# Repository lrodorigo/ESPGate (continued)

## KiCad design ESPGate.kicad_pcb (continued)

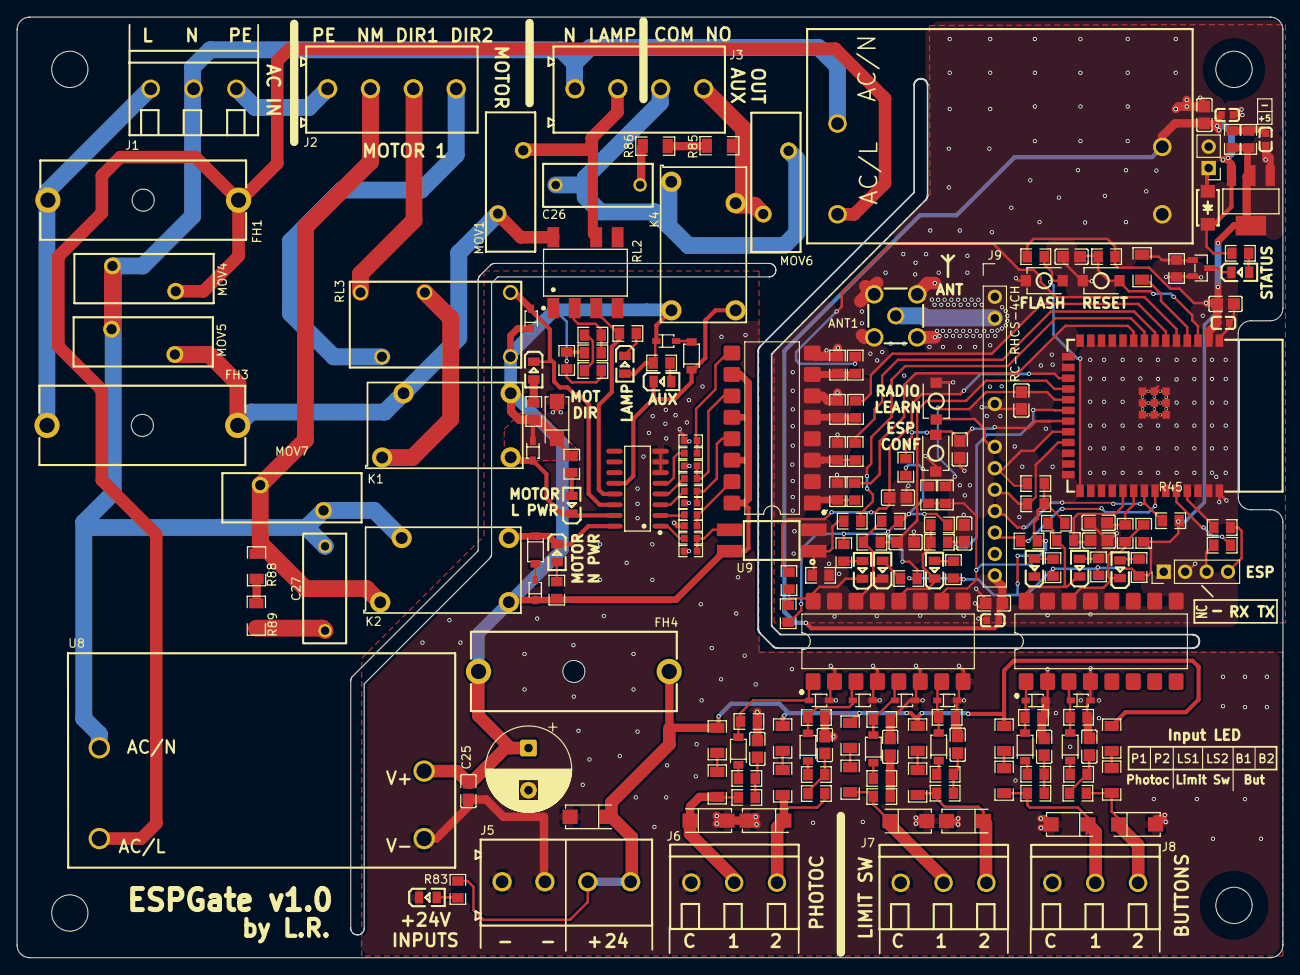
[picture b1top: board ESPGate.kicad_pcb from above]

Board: 2 copper layers, 150.1 x 111.5 mm, 203 parts (0 on the bottom side), 125 nets.

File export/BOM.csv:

"Reference","Qty","Value","LCSC Part","DNP","Exclude from Simulation","Exclude from Position Files","Description"
"C5,C18","2","470uF","","DNP","","${EXCLUDE_FROM_POS_FILES}","Polarized capacitor"
"J4","1","Conn_01x04_Pin","","","","${EXCLUDE_FROM_POS_FILES}","Generic connector, single row, 01x04, script generated"
"R1","1","1","C25271","","","${EXCLUDE_FROM_POS_FILES}","Resistor"
"R2,R16,R22,R25,R29,R35,R44","7","330","C17630","","","${EXCLUDE_FROM_POS_FILES}","Resistor"
"R3,R4,R6,R9,R11,R14,R18,R20,R21,R23,R24,R26,R27,R53,R54,R55,R56,R57,R58,R83","20","10k","C17414","","","${EXCLUDE_FROM_POS_FILES}","Resistor"
"R7,R8,R10,R12,R13,R15,R17,R19","8","1.2k","C17379","","","${EXCLUDE_FROM_POS_FILES}","Resistor"
"R30,R31,R32,R33,R34,R37","6","6.8k","C17772","","","${EXCLUDE_FROM_POS_FILES}","Resistor"
"R36,R39,R40,R41,R42,R43,R46,R47,R48,R49,R50,R51,R77,R78,R79,R80,R81,R82","18","1k","C17513","","","${EXCLUDE_FROM_POS_FILES}","Resistor"
"R65,R66,R67,R68,R69,R70","6","100","C17408","","","${EXCLUDE_FROM_POS_FILES}","Resistor"
"R5,R28,R38,R45,R52","5","100","C17901","","","${EXCLUDE_FROM_POS_FILES}","Resistor"
"R59,R60,R61,R62,R63,R64","6","1k","C4410","","","${EXCLUDE_FROM_POS_FILES}","Resistor"
"R71,R72,R73,R74,R75,R76","6","2k","C17944","","","${EXCLUDE_FROM_POS_FILES}","Resistor"
"C1,C2,C7","3","10uF","C19702","","","${EXCLUDE_FROM_POS_FILES}","Unpolarized capacitor"
"C3,C6,C8,C9,C10,C12,C13,C14,C15,C16,C25","11","100nF","C28233","","","${EXCLUDE_FROM_POS_FILES}","Unpolarized capacitor"
"C4","1","1uF","C28323","","","${EXCLUDE_FROM_POS_FILES}","Unpolarized capacitor"
"C19,C20,C21,C22,C23,C24","6","4.7uF","C1779","","","${EXCLUDE_FROM_POS_FILES}","Unpolarized capacitor"
"C11,C17","2","22nF","C390050","","","${EXCLUDE_FROM_POS_FILES}",""
"J1,J6,J7,J8","4","Screw_Terminal_01x03","","","","${EXCLUDE_FROM_POS_FILES}","Generic screw terminal, single row, 01x03, script generated (kicad-library-utils/schlib/autogen/connector/)"
"J2,J3,J5","3","Screw_Terminal_01x04","","","","${EXCLUDE_FROM_POS_FILES}","Generic screw terminal, single row, 01x04, script generated (kicad-library-utils/schlib/autogen/connector/)"
"FH1,FH2,FH3,FH4","4","PTF-77","C717030","","","${EXCLUDE_FROM_POS_FILES}",""
"NTC1","1","KH-2.54PH180-1X3P-L11.5","C2932698","DNP","","${EXCLUDE_FROM_POS_FILES}",""
"LED1,LED12","2","17-21SUYC/TR8","C2297","","","${EXCLUDE_FROM_POS_FILES}",""
"LED2,LED3,LED4,LED6,LED7,LED8,LED9,LED10,LED11","9","NCD0805R1","C84256","","","${EXCLUDE_FROM_POS_FILES}",""
"LED5","1","0805G (Green)","C2297","","","${EXCLUDE_FROM_POS_FILES}",""
"U8","1","IRM-10-24_C5127809","C5127809","","","${EXCLUDE_FROM_POS_FILES}",""
"U1","1","IRM-05-5","C48603696","","","${EXCLUDE_FROM_POS_FILES}",""
"RL3","1","G5Q-14-DC24","C397242","","","${EXCLUDE_FROM_POS_FILES}",""
"RL4","1","HF140FF/024-2ZSTF","C5322992","","","${EXCLUDE_FROM_POS_FILES}",""
"RN1","1","4x 10k","C29718","","","${EXCLUDE_FROM_POS_FILES}",""
"MOV1,MOV2,MOV3,MOV4,MOV5","5","14D471K_C8852","C8852","","","${EXCLUDE_FROM_POS_FILES}","Voltage dependent resistor"
"D5","1","SS14","C2480","","","${EXCLUDE_FROM_POS_FILES}",""
"D2,D18,D19,D20,D21,D22,D23,D24","8","SMAJ26A-C148225","C148225","","","${EXCLUDE_FROM_POS_FILES}",""
"RL1,RL2","2","BC2223A","C596513","","","${EXCLUDE_FROM_POS_FILES}",""
"D4,D12,D13,D14,D15,D16,D17","7","BZT52C10_C19077408","C19077408","","","${EXCLUDE_FROM_POS_FILES}",""
"D1,D3","2","1N4148WS T4","C2128","","","${EXCLUDE_FROM_POS_FILES}",""
"D6,D7,D8,D9,D10,D11","6","1N4148","C2128","","","${EXCLUDE_FROM_POS_FILES}",""
"U5","1","ULN2003ADR","C7512","","","${EXCLUDE_FROM_POS_FILES}","High Voltage, High Current Darlington Transistor Arrays, SOIC16/SOIC16W/DIP16/TSSOP16"
"U2","1","AMS1117-3.3","C6186","","","${EXCLUDE_FROM_POS_FILES}",""
"Q1","1","2N7002","C8545","","","${EXCLUDE_FROM_POS_FILES}",""
"SW1,SW2,SW3","3","TS-1088-AR02016","C720477","","","${EXCLUDE_FROM_POS_FILES}",""
"U3","1","ESP32-S3-WROOM-1-N4R8","C2913200","","","${EXCLUDE_FROM_POS_FILES}",""
"U4,U6,U7","3","LTV-847S","C114599","","","${EXCLUDE_FROM_POS_FILES}","DC Optocoupler, Vce 35V, CTR 50%, SMDIP-16"
